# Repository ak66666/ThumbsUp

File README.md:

# 44 Keys Board "Thumbs Up!"

44-key Split Keyboard PCB with the thumb keys placed on the raised platforms.

Ideas behind this design and layout are described here:

The naked PCB approach is borrowed from Georgi created by Germ @GBoards.ca

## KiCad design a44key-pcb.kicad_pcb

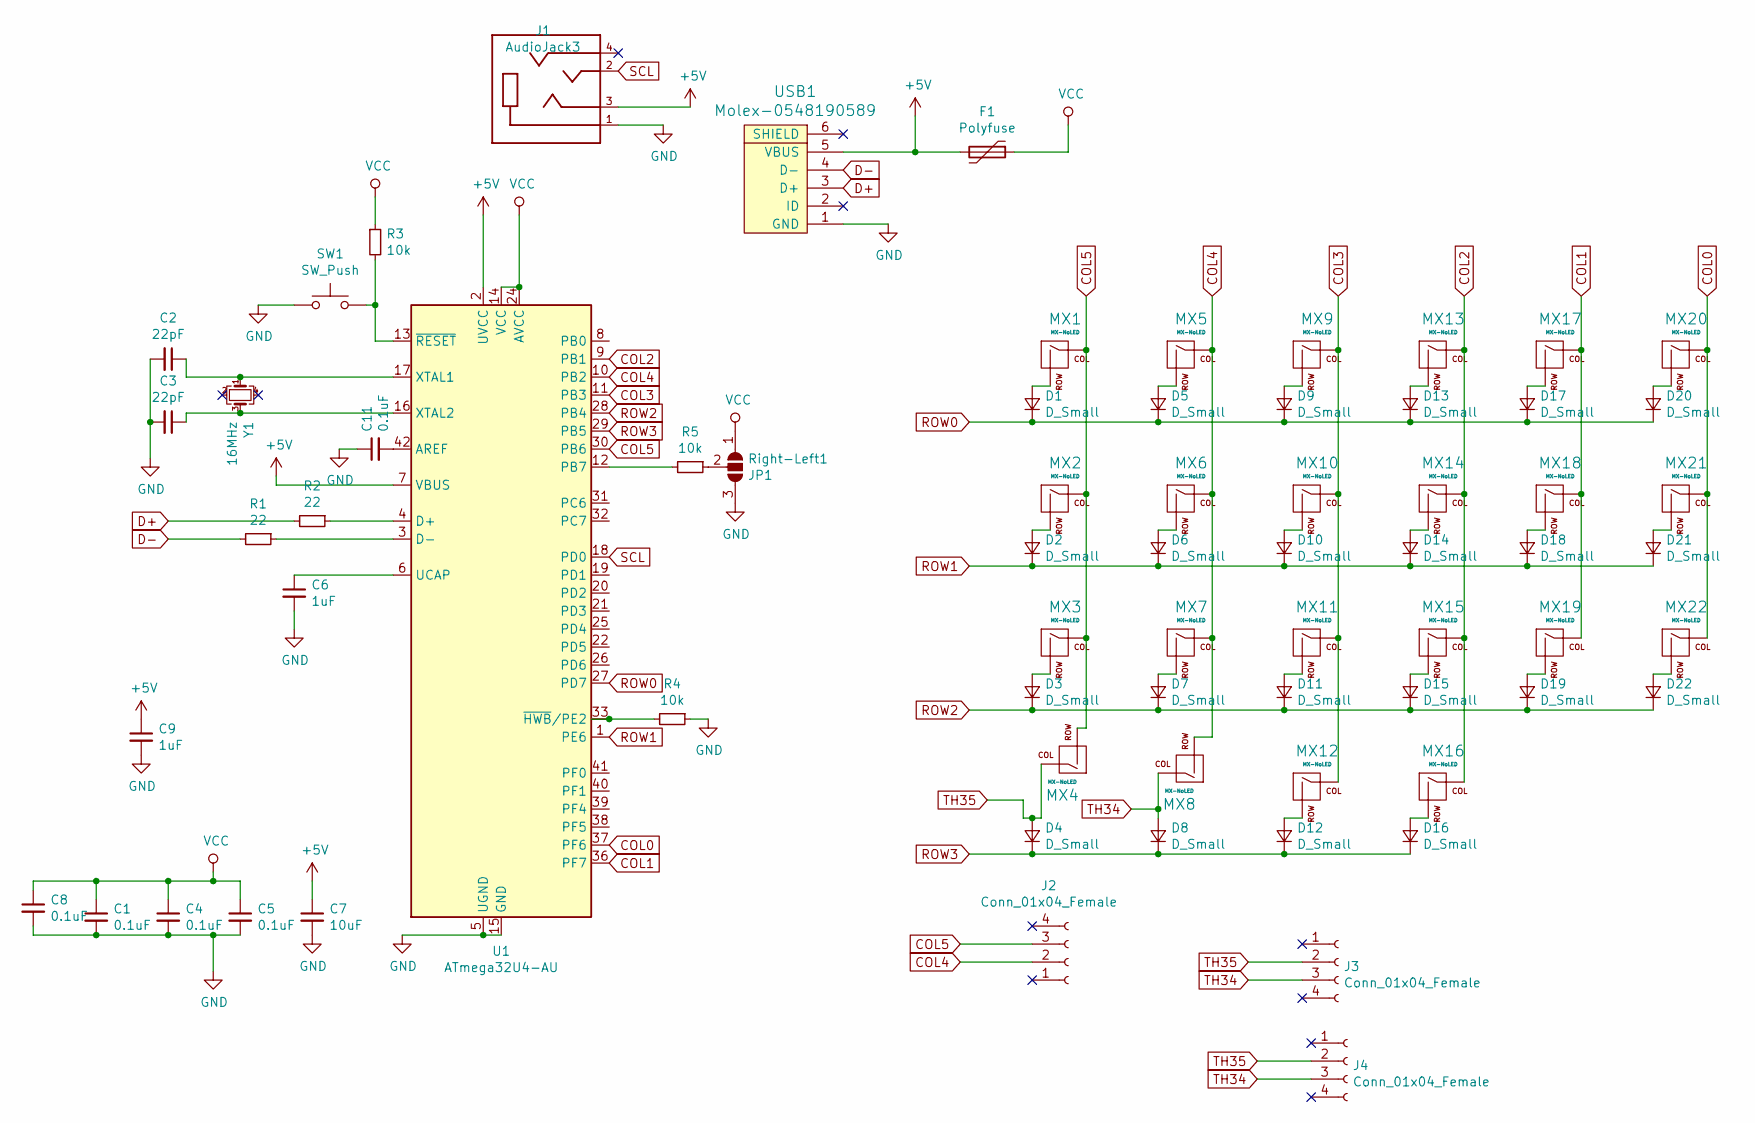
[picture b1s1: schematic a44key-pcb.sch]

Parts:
C1, C4, C5, C8, C11: 0.1uF; C_0805_2012Metric
C2, C3: 22pF; C_0805_2012Metric
C6, C9: 1uF; C_0805_2012Metric
C7: 10uF; C_0805_2012Metric
D1, D2, D3, D4, D5, D6, D7, D8, D9, D10, D11, D12, D13, D14, D15, D16, D17, D18, D19, D20, D21, D22: D_Small; D_SOD-123
F1: Polyfuse; Fuse_1206_3216Metric
J1: AudioJack3; CUI_SJ-43514
J2, J3, J4: Conn_01x04_Female; PinHeader_1x04_P2.54mm_Vertical
MX1, MX2, MX3, MX4, MX5, MX6, MX7, MX8, MX9, MX10, MX11, MX12, MX13, MX14, MX15, MX16, MX17, MX18, MX19, MX20, MX21, MX22: MX-NoLED; MX-Alps-Choc-X-1U-NoLED
R1, R2: 22; R_0805_2012Metric
R3, R4, R5: 10k; R_0805_2012Metric
Right-Left1: JP1; SolderJumper-3_P1.3mm_Open_Pad1.0x1.5mm
SW1: SW_Push; SKQG-1155865
U1: ATmega32U4-AU; TQFP-44_10x10mm_P0.8mm
USB1: Molex-0548190589
Y1: 16MHz; Crystal_SMD_3225-4Pin_3.2x2.5mm_HandSoldering

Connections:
+5V: C7.1, C9.1, F1.2, J1.3, U1.2 (UVCC), U1.7 (VBUS), USB1.5 (VBUS)
COL0: MX20.1 (COL), MX21.1 (COL), MX22.1 (COL), U1.37 (PF6)
COL1: MX17.1 (COL), MX18.1 (COL), MX19.1 (COL), U1.36 (PF7)
COL2: MX13.1 (COL), MX14.1 (COL), MX15.1 (COL), MX16.1 (COL), U1.9 (PB1)
COL3: MX9.1 (COL), MX10.1 (COL), MX11.1 (COL), MX12.1 (COL), U1.11 (PB3)
COL4: J2.2, MX5.1 (COL), MX6.1 (COL), MX7.1 (COL), MX8.2 (ROW), U1.10 (PB2)
COL5: J2.3, MX1.1 (COL), MX2.1 (COL), MX3.1 (COL), MX4.2 (ROW), U1.30 (PB6)
D+: R2.2, USB1.3 (D+)
D-: R1.2, USB1.4 (D-)
GND: C1.2, C2.2, C3.2, C4.2, C5.2, C6.2, C7.2, C8.2, C9.2, C11.1, J1.1, R4.1, Right-Left1.3 (B), SW1.1, U1.5 (UGND), U1.15 (GND), U1.23 (GND), U1.35 (GND), U1.43 (GND), USB1.1 (GND)
unnamed: C2.1, U1.17 (XTAL1), Y1.1
unnamed: C3.1, U1.16 (XTAL2), Y1.3
unnamed: C6.1, U1.6 (UCAP)
unnamed: C11.2, U1.42 (AREF)
unnamed: D1.2 (A), MX1.2 (ROW)
unnamed: D2.2 (A), MX2.2 (ROW)
unnamed: D3.2 (A), MX3.2 (ROW)
unnamed: D5.2 (A), MX5.2 (ROW)
unnamed: D6.2 (A), MX6.2 (ROW)
unnamed: D7.2 (A), MX7.2 (ROW)
unnamed: D9.2 (A), MX9.2 (ROW)
unnamed: D10.2 (A), MX10.2 (ROW)
unnamed: D11.2 (A), MX11.2 (ROW)
unnamed: D12.2 (A), MX12.2 (ROW)
unnamed: D13.2 (A), MX13.2 (ROW)
unnamed: D14.2 (A), MX14.2 (ROW)
unnamed: D15.2 (A), MX15.2 (ROW)
unnamed: D16.2 (A), MX16.2 (ROW)
unnamed: D17.2 (A), MX17.2 (ROW)
unnamed: D18.2 (A), MX18.2 (ROW)
unnamed: D19.2 (A), MX19.2 (ROW)
unnamed: D20.2 (A), MX20.2 (ROW)
unnamed: D21.2 (A), MX21.2 (ROW)
unnamed: D22.2 (A), MX22.2 (ROW)
unnamed: R1.1, U1.3 (D-)
unnamed: R2.1, U1.4 (D+)
unnamed: R3.2, SW1.2, U1.13 (~RESET)
unnamed: R4.2, U1.33 (~HWB~/PE2)
unnamed: R5.1, Right-Left1.2 (C)
unnamed: R5.2, U1.12 (PB7)
ROW0: D1.1 (K), D5.1 (K), D9.1 (K), D13.1 (K), D17.1 (K), D20.1 (K), U1.27 (PD7)
ROW1: D2.1 (K), D6.1 (K), D10.1 (K), D14.1 (K), D18.1 (K), D21.1 (K), U1.1 (PE6)
ROW2: D3.1 (K), D7.1 (K), D11.1 (K), D15.1 (K), D19.1 (K), D22.1 (K), U1.28 (PB4)
ROW3: D4.1 (K), D8.1 (K), D12.1 (K), D16.1 (K), U1.29 (PB5)
SCL: J1.2, U1.18 (PD0)
TH34: D8.2 (A), J3.3, J4.3, MX8.1 (COL)
TH35: D4.2 (A), J3.2, J4.2, MX4.1 (COL)
VCC: C1.1, C4.1, C5.1, C8.1, F1.1, R3.1, Right-Left1.1 (A), U1.14 (VCC), U1.24 (AVCC), U1.34 (VCC), U1.44 (AVCC)

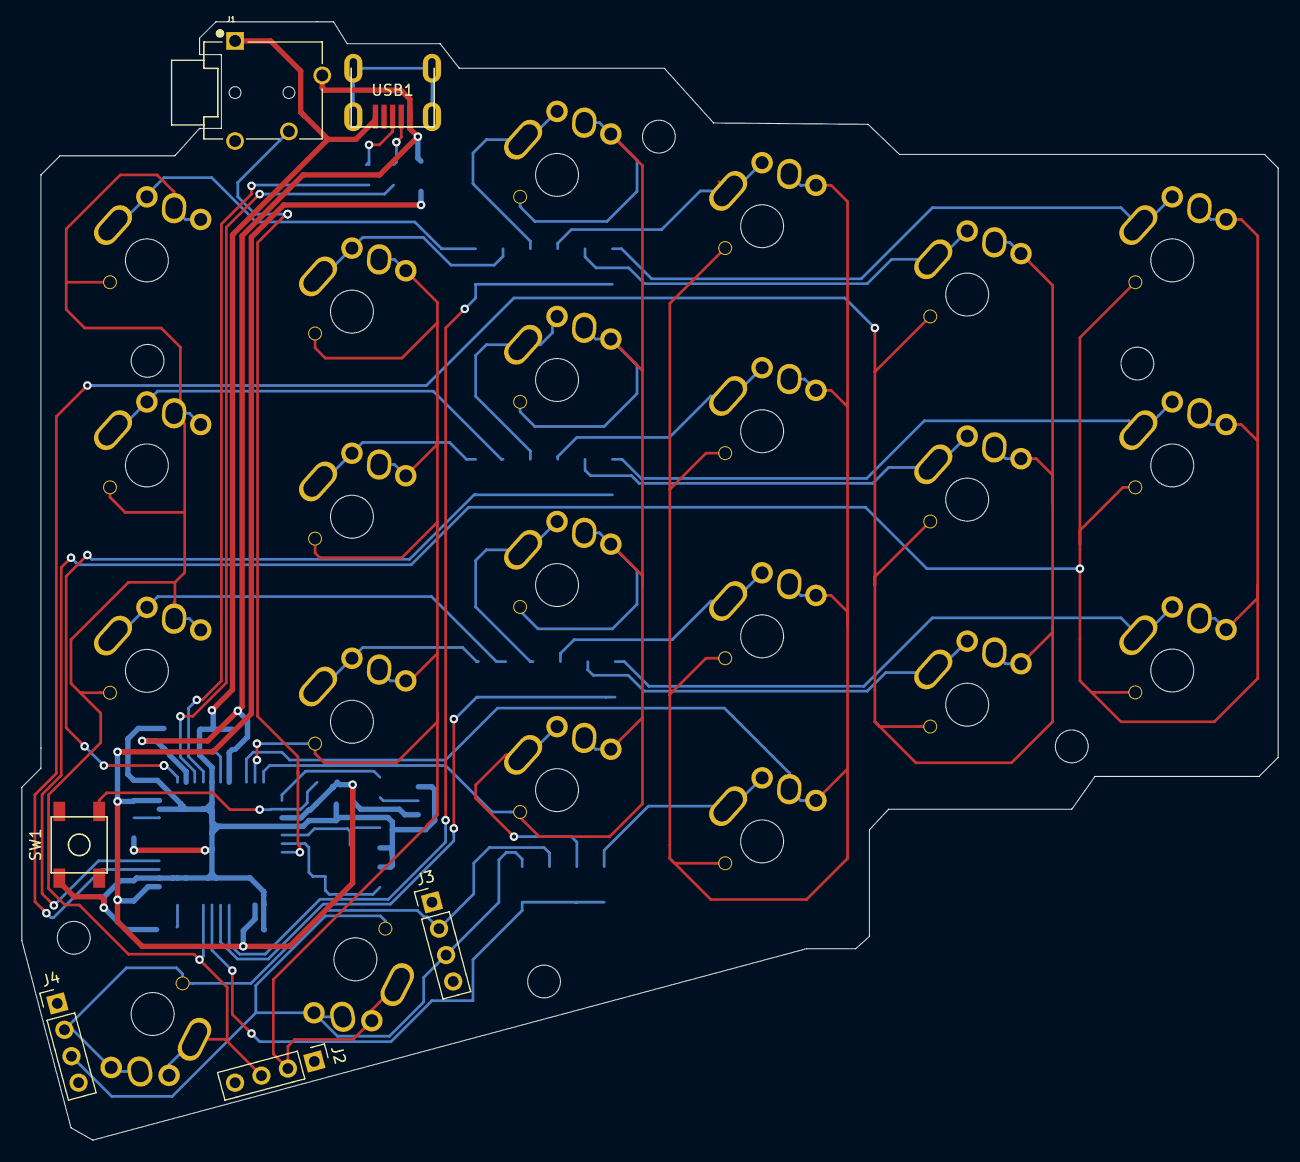
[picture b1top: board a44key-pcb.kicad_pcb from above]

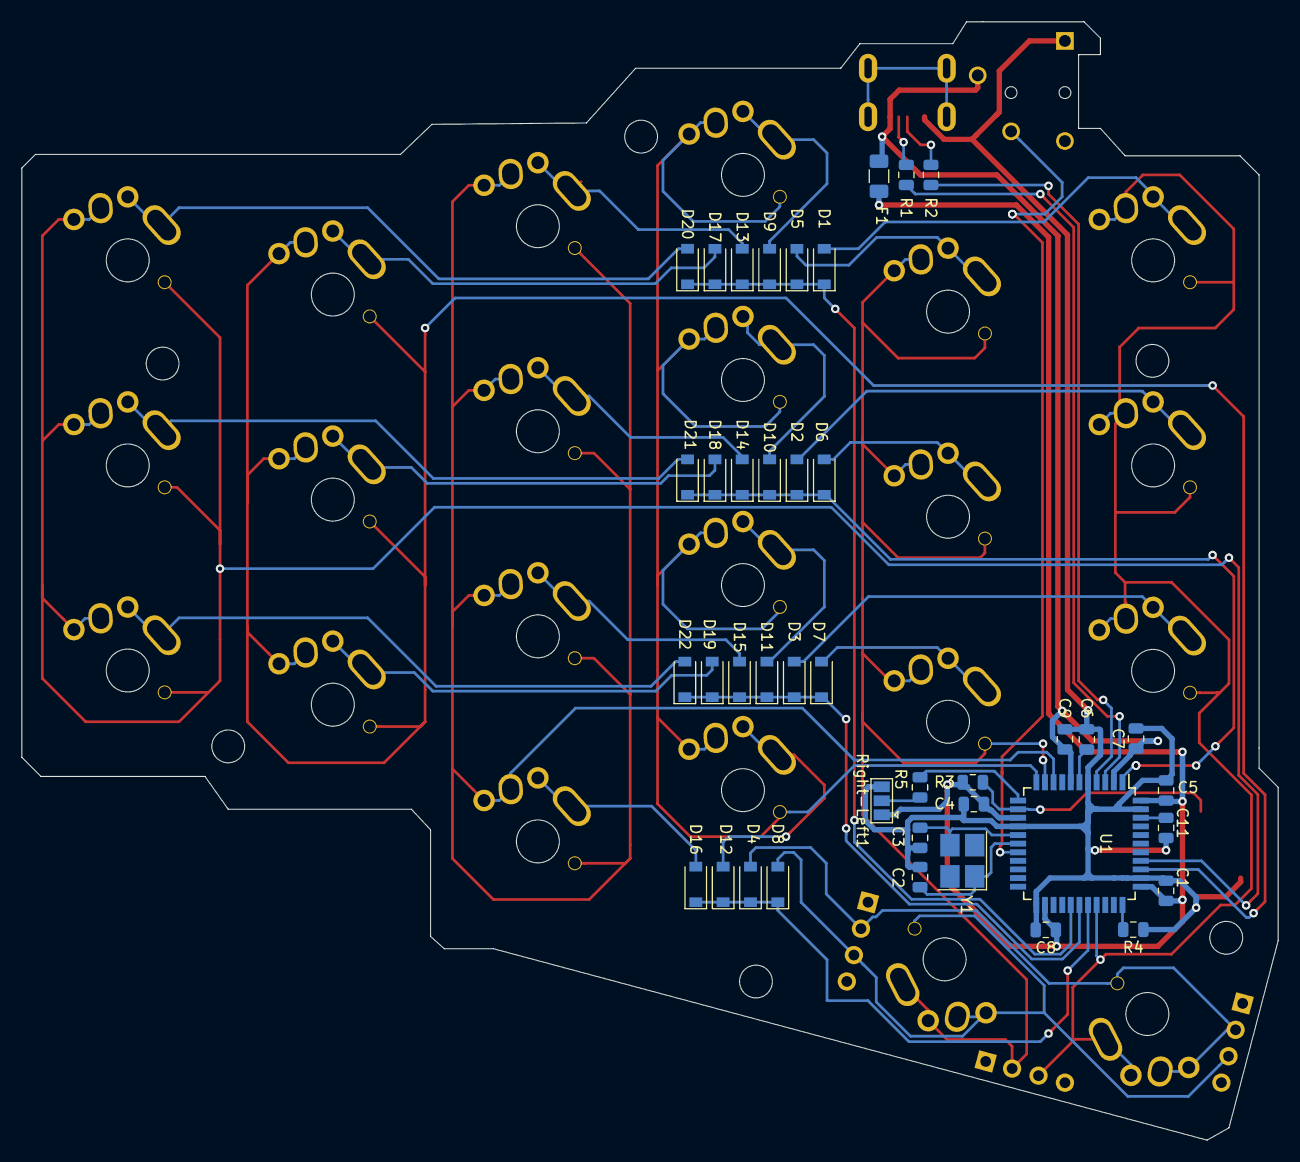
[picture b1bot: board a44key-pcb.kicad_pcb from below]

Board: 2 copper layers, 116.7 x 103.9 mm, 69 parts (41 on the bottom side), 48 nets.

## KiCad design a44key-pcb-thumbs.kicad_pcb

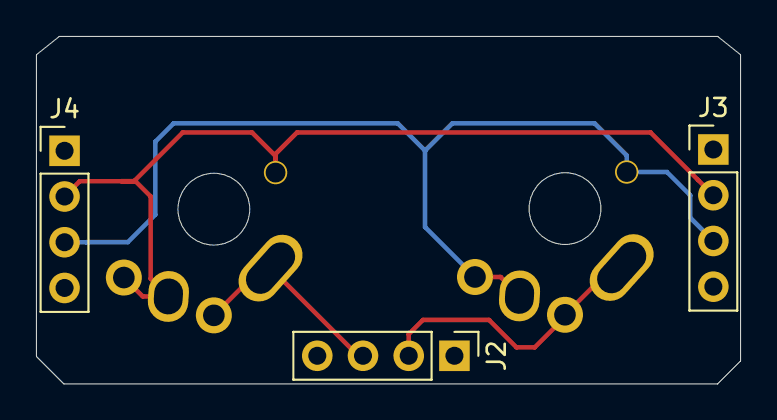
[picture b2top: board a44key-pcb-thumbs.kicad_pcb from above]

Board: 2 copper layers, 39.1 x 19.3 mm, 5 parts (0 on the bottom side), 4 nets.

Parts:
J2, J3, J4: Conn_01x04_Female; PinHeader_1x04_P2.54mm_Vertical
MX4, MX8: MX-NoLED; MX-Alps-Choc-X-1U-NoLED

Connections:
COL4: J2.2, MX8.2
COL5: J2.3, MX4.2
TH34: J3.3, J4.3, MX8.1
TH35: J3.2, J4.2, MX4.1

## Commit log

2021-10-16 KiCAD project added.
    KiCAD Project created
2021-10-16 Submodules added
2021-10-16 Create fp-lib-table
2021-10-18 Somewhat ready
2021-10-18 Gerbers created
2021-10-19 Rewired
2021-10-22 Covered with zones
2021-10-22 Generated Gerbers
2021-11-10 Added raisers for the thumbs
2021-11-10 Rerouting
2021-11-10 Breakout added
2021-11-11 Gerbers generated
2022-01-06 Added the footprint libraries
2022-01-06 {PCB
2022-01-07 PCB Left Hand Added
2022-01-08 PCB Thumbs Raiser Added
2022-01-14 BOM added
2022-01-21 Added a picture of the build 20220121
2022-01-21 Update README.md
    Added pictures into the description.
2022-01-24 Added parameters for the modifier to work nicelyDD
2022-01-24 Fixed the traces for the hand choosing jumper
2022-01-31 Photos of a Kailh Choc version
2022-01-31 Added more pictures with Kailh Choc part
